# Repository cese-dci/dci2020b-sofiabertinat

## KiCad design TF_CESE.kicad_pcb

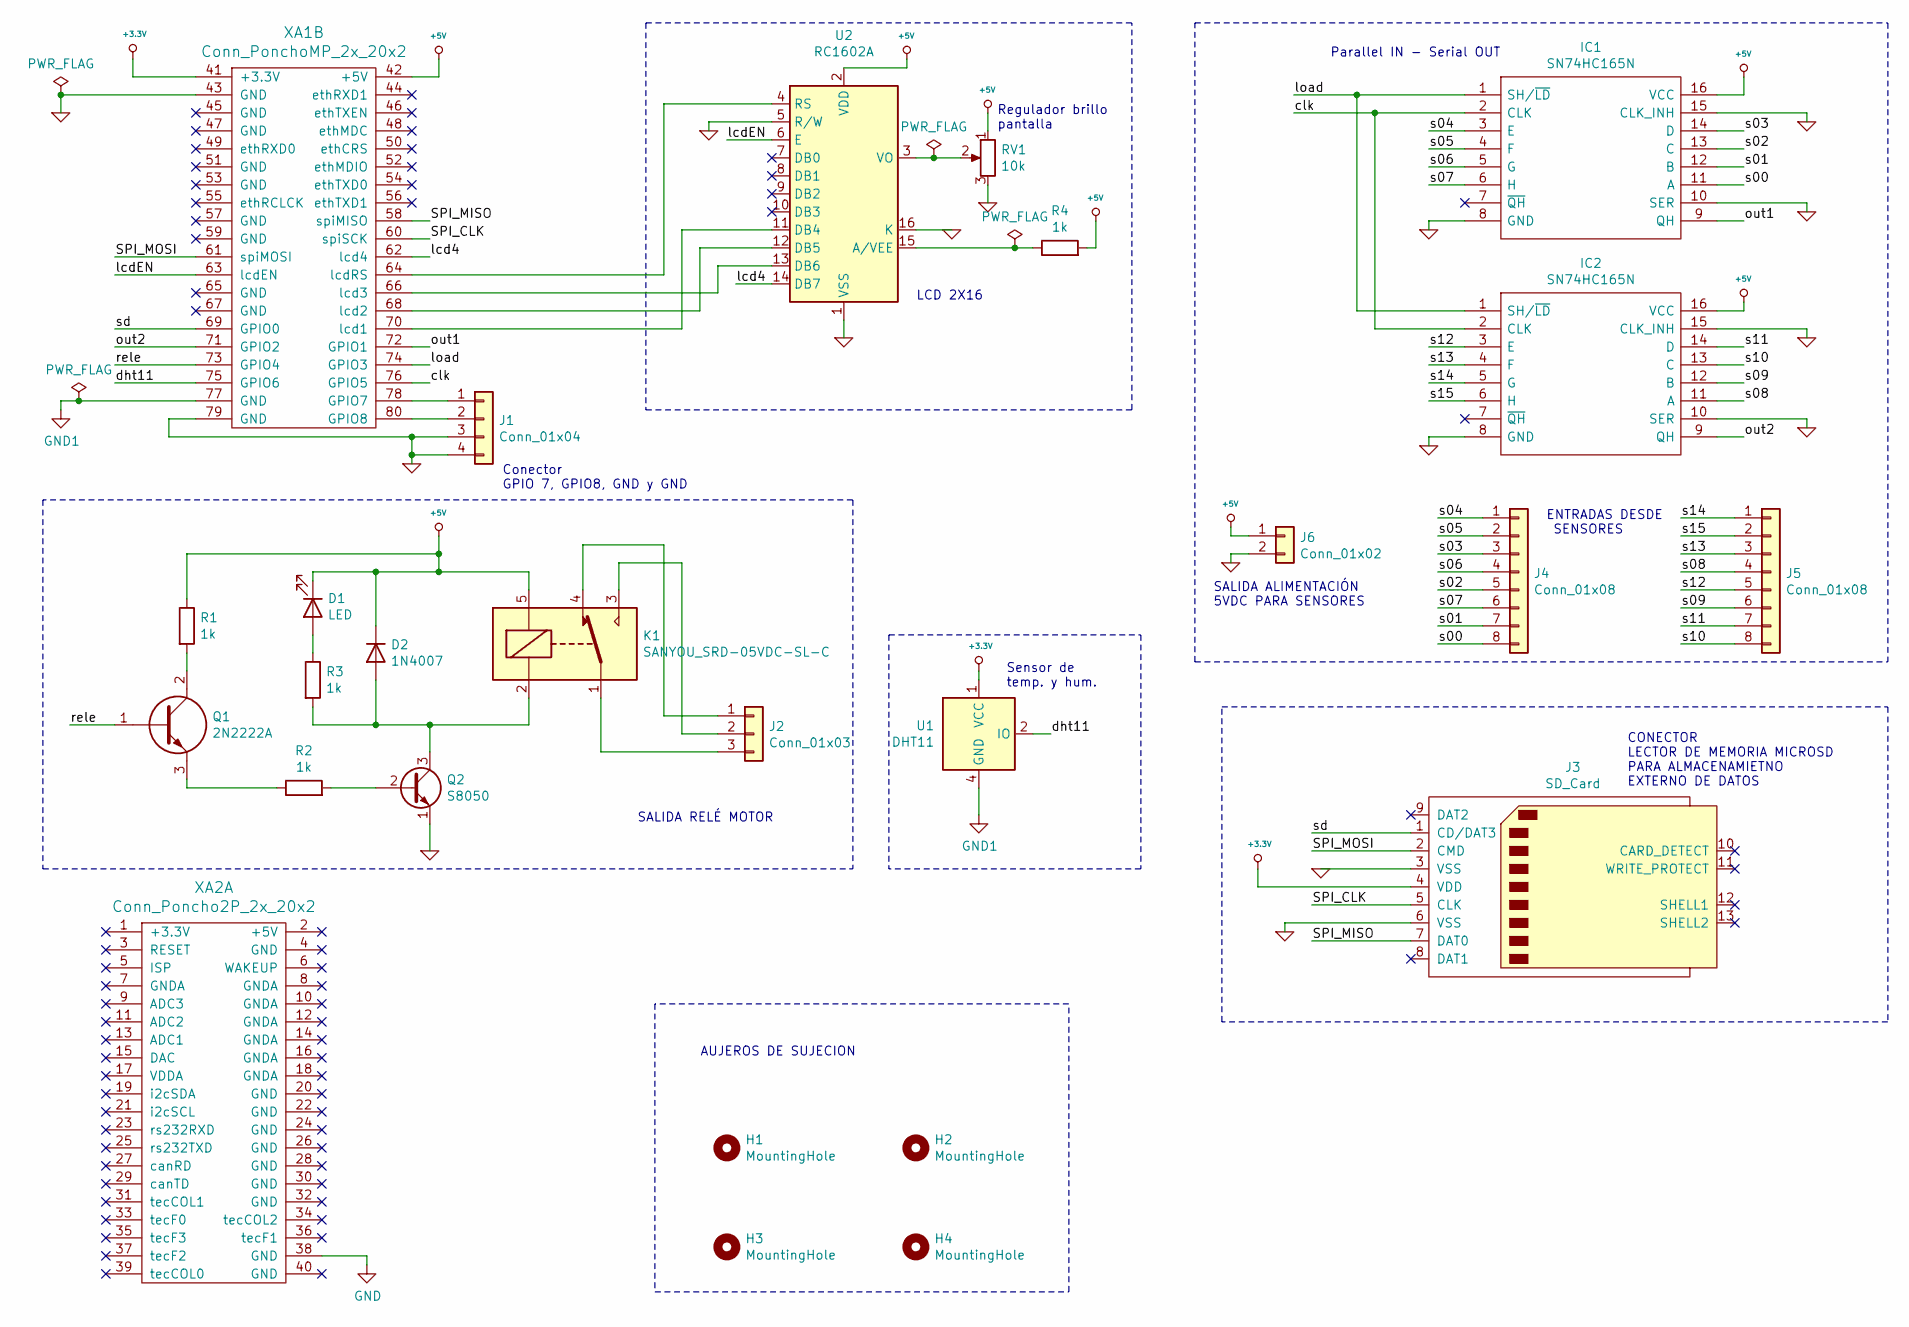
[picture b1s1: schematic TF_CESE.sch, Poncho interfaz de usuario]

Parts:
D1: LED; LED_D3.0mm
D2: 1N4007; D_DO-41_SOD81_P10.16mm_Horizontal
H1, H2: MountingHole; MountingHole_3.7mm
H3: MountingHole; MountingHole_2.7mm
H4: MountingHole; MountingHole_2.1mm
IC1, IC2: SN74HC165N; DIP-18_W7.62mm_Socket_LongPads; Manufacturer_Part_Number SN74HC165N; Mouser Part Number 595-SN74HC165N
J1: Conn_01x04; PinSocket_1x04_P2.54mm_Vertical
J2: Conn_01x03; TerminalBlock_Phoenix_MKDS-1,5-3-5.08_1x03_P5.08mm_Horizont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
J3: SD_Card; SD_Kyocera_145638009211859+
J4, J5: Conn_01x08; IDC-Header_2x04_P2.54mm_Vertical
J6: Conn_01x02; TerminalBlock_Phoenix_MKDS-1,5-2-5.08_1x02_P5.08mm_Horizont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
K1: SANYOU_SRD-05VDC-SL-C; Relay_SPDT_SANYOU_SRD_Series_Form_C; Part numer SRD-05VDC-SL-C
Q1: 2N2222A; TO-18_4; Manufacturer_Part_Number 2N2222A; Mouser Part Number 511-2N2222A
Q2: S8050; TO-92_Inline; Part number S8050L-x-T92-B
R1, R2, R3, R4: 1k; R_Axial_DIN0207_L6.3mm_D2.5mm_P10.16mm_Horizontal
RV1: 10k; Potentiometer_Vishay_T73XX_Horizontal
U1: DHT11; Aosong_DHT11_5.5x12.0_P2.54mm
U2: RC1602A
XA1: Conn_PonchoMP_2x_20x2; Conn_Poncho_Izquierdo
XA2: Conn_Poncho2P_2x_20x2; Conn_Poncho_Derecha

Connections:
+3.3V: J3.4 (VDD), U1.1 (VCC), XA1.41 (+3.3V)
+5V: D1.1 (K), D2.1 (K), IC1.16 (VCC), IC2.16 (VCC), J6.1, K1.5, R1.1, R4.2, RV1.1, U2.2 (VDD), XA1.42 (+5V)
/SPI_CLK: J3.5 (CLK), XA1.60 (spiSCK)
/SPI_MISO: J3.7 (DAT0), XA1.58 (spiMISO)
/SPI_MOSI: J3.2 (CMD), XA1.61 (spiMOSI)
/clk: IC1.2 (CLK), IC2.2 (CLK), XA1.76 (GPIO5)
/dht11: U1.2 (IO), XA1.75 (GPIO6)
/lcd4: U2.14 (DB7), XA1.62 (lcd4)
/lcdEN: U2.6 (E), XA1.63 (lcdEN)
/load: IC1.1 (SH/~LD), IC2.1 (SH/~LD), XA1.74 (GPIO3)
/out1: IC1.9 (QH), XA1.72 (GPIO1)
/out2: IC2.9 (QH), XA1.71 (GPIO2)
/rele: Q1.1, XA1.73 (GPIO4)
/s00: IC1.11 (A), J4.8
/s01: IC1.12 (B), J4.7
/s02: IC1.13 (C), J4.5
/s03: IC1.14 (D), J4.3
/s04: IC1.3 (E), J4.1
/s05: IC1.4 (F), J4.2
/s06: IC1.5 (G), J4.4
/s07: IC1.6 (H), J4.6
/s08: IC2.11 (A), J5.4
/s09: IC2.12 (B), J5.6
/s10: IC2.13 (C), J5.8
/s11: IC2.14 (D), J5.7
/s12: IC2.3 (E), J5.5
/s13: IC2.4 (F), J5.3
/s14: IC2.5 (G), J5.1
/s15: IC2.6 (H), J5.2
/sd: J3.1 (CD/DAT3), XA1.69 (GPIO0)
GND: IC1.8 (GND), IC1.10 (SER), IC1.15 (CLK_INH), IC2.8 (GND), IC2.10 (SER), IC2.15 (CLK_INH), J1.3, J1.4, J3.3 (VSS), J3.6 (VSS), J6.2, Q2.1 (E), RV1.3, U2.1 (VSS), U2.5 (R/W), U2.16 (K), XA1.43 (GND), XA1.79 (GND), XA2.38 (GND)
GND1: U1.4 (GND), XA1.77 (GND)
unnamed: D1.2 (A), R3.1
unnamed: D2.2 (A), K1.2, Q2.3 (C), R3.2
unnamed: J1.1, XA1.78 (GPIO7)
unnamed: J1.2, XA1.80 (GPIO8)
unnamed: J2.1, K1.4
unnamed: J2.2, K1.3
unnamed: J2.3, K1.1
unnamed: Q1.2, R1.2
unnamed: Q1.3, R2.1
unnamed: Q2.2 (B), R2.2
unnamed: R4.1, U2.15 (A/VEE)
unnamed: RV1.2, U2.3 (VO)
unnamed: U2.4 (RS), XA1.64 (lcdRS)
unnamed: U2.11 (DB4), XA1.70 (lcd1)
unnamed: U2.12 (DB5), XA1.68 (lcd2)
unnamed: U2.13 (DB6), XA1.66 (lcd3)

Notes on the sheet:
Parallel IN - Serial OUT
LCD 2X16
SALIDA RELÉ MOTOR
ENTRADAS DESDE SENSORES
Sensor de temp. y hum.
Conector GPIO 7, GPIO8, GND y GND
SALIDA ALIMENTACIÓN 5VDC PARA SENSORES
CONECTOR LECTOR DE MEMORIA MICROSD PARA ALMACENAMIETNO EXTERNO DE DATOS
Regulador brillo pantalla
AUJEROS DE SUJECION

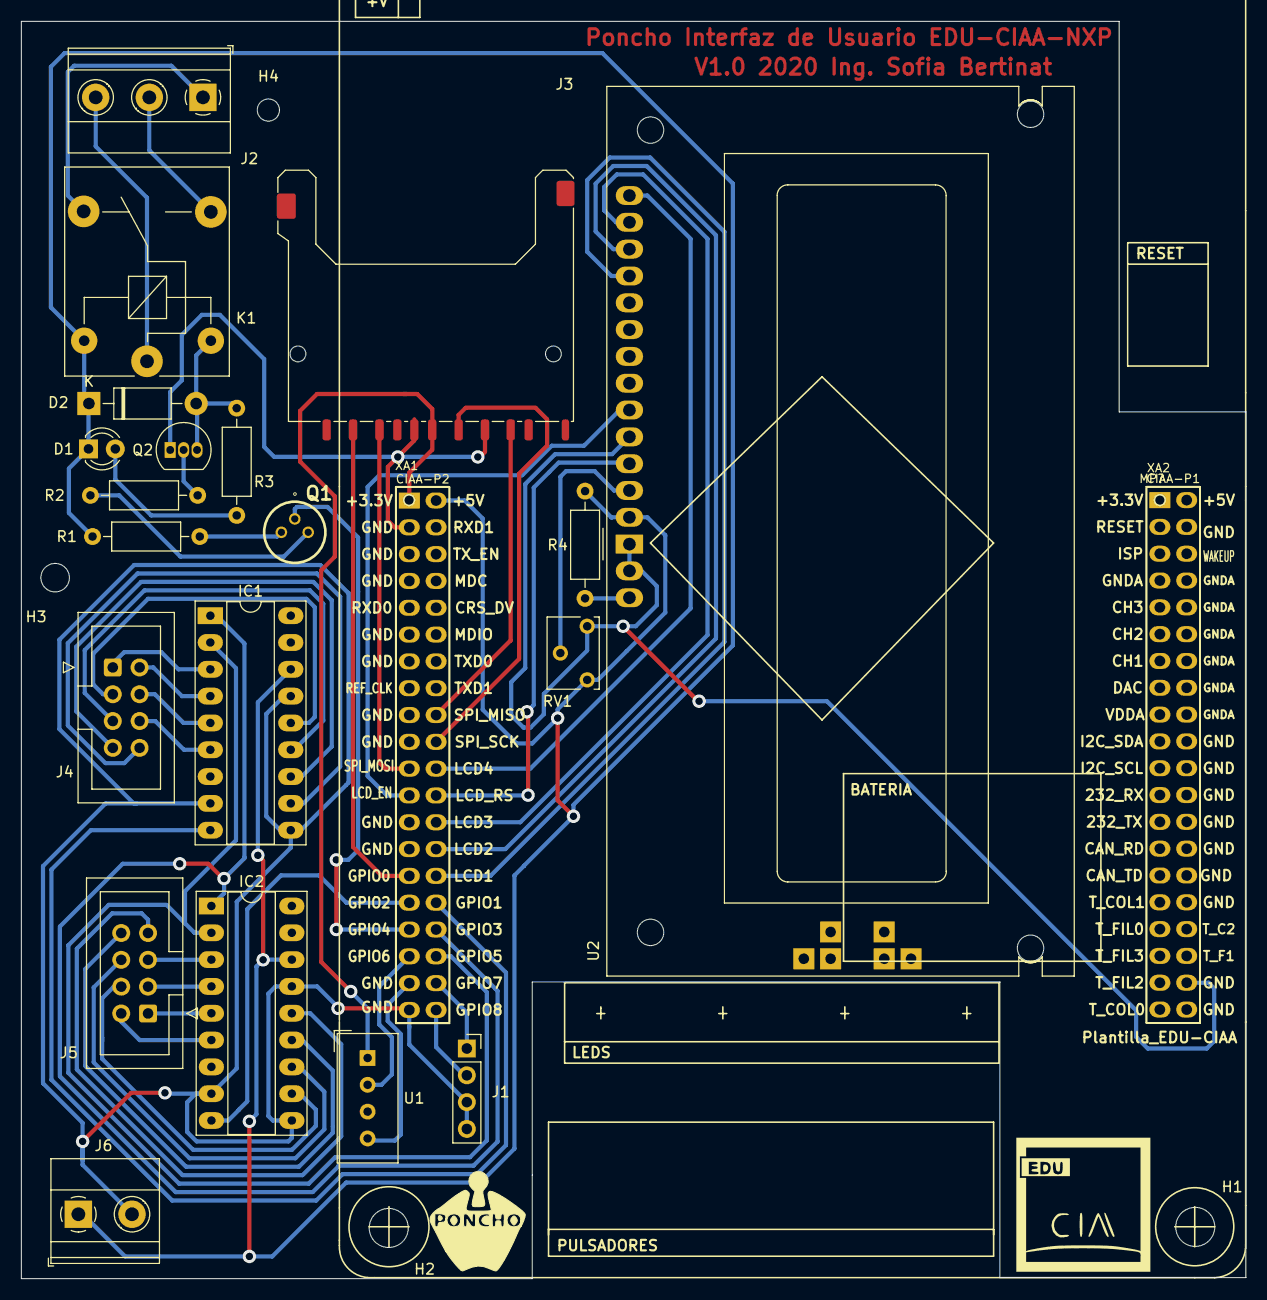
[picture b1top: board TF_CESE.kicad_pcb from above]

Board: 2 copper layers, 116.0 x 119.1 mm, 27 parts (0 on the bottom side), 48 nets.

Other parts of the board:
MP?: Plantilla_EDU-CIAA

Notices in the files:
TF_CESE.kicad_pcb:
Copyright  INIA - Licencia BSD
